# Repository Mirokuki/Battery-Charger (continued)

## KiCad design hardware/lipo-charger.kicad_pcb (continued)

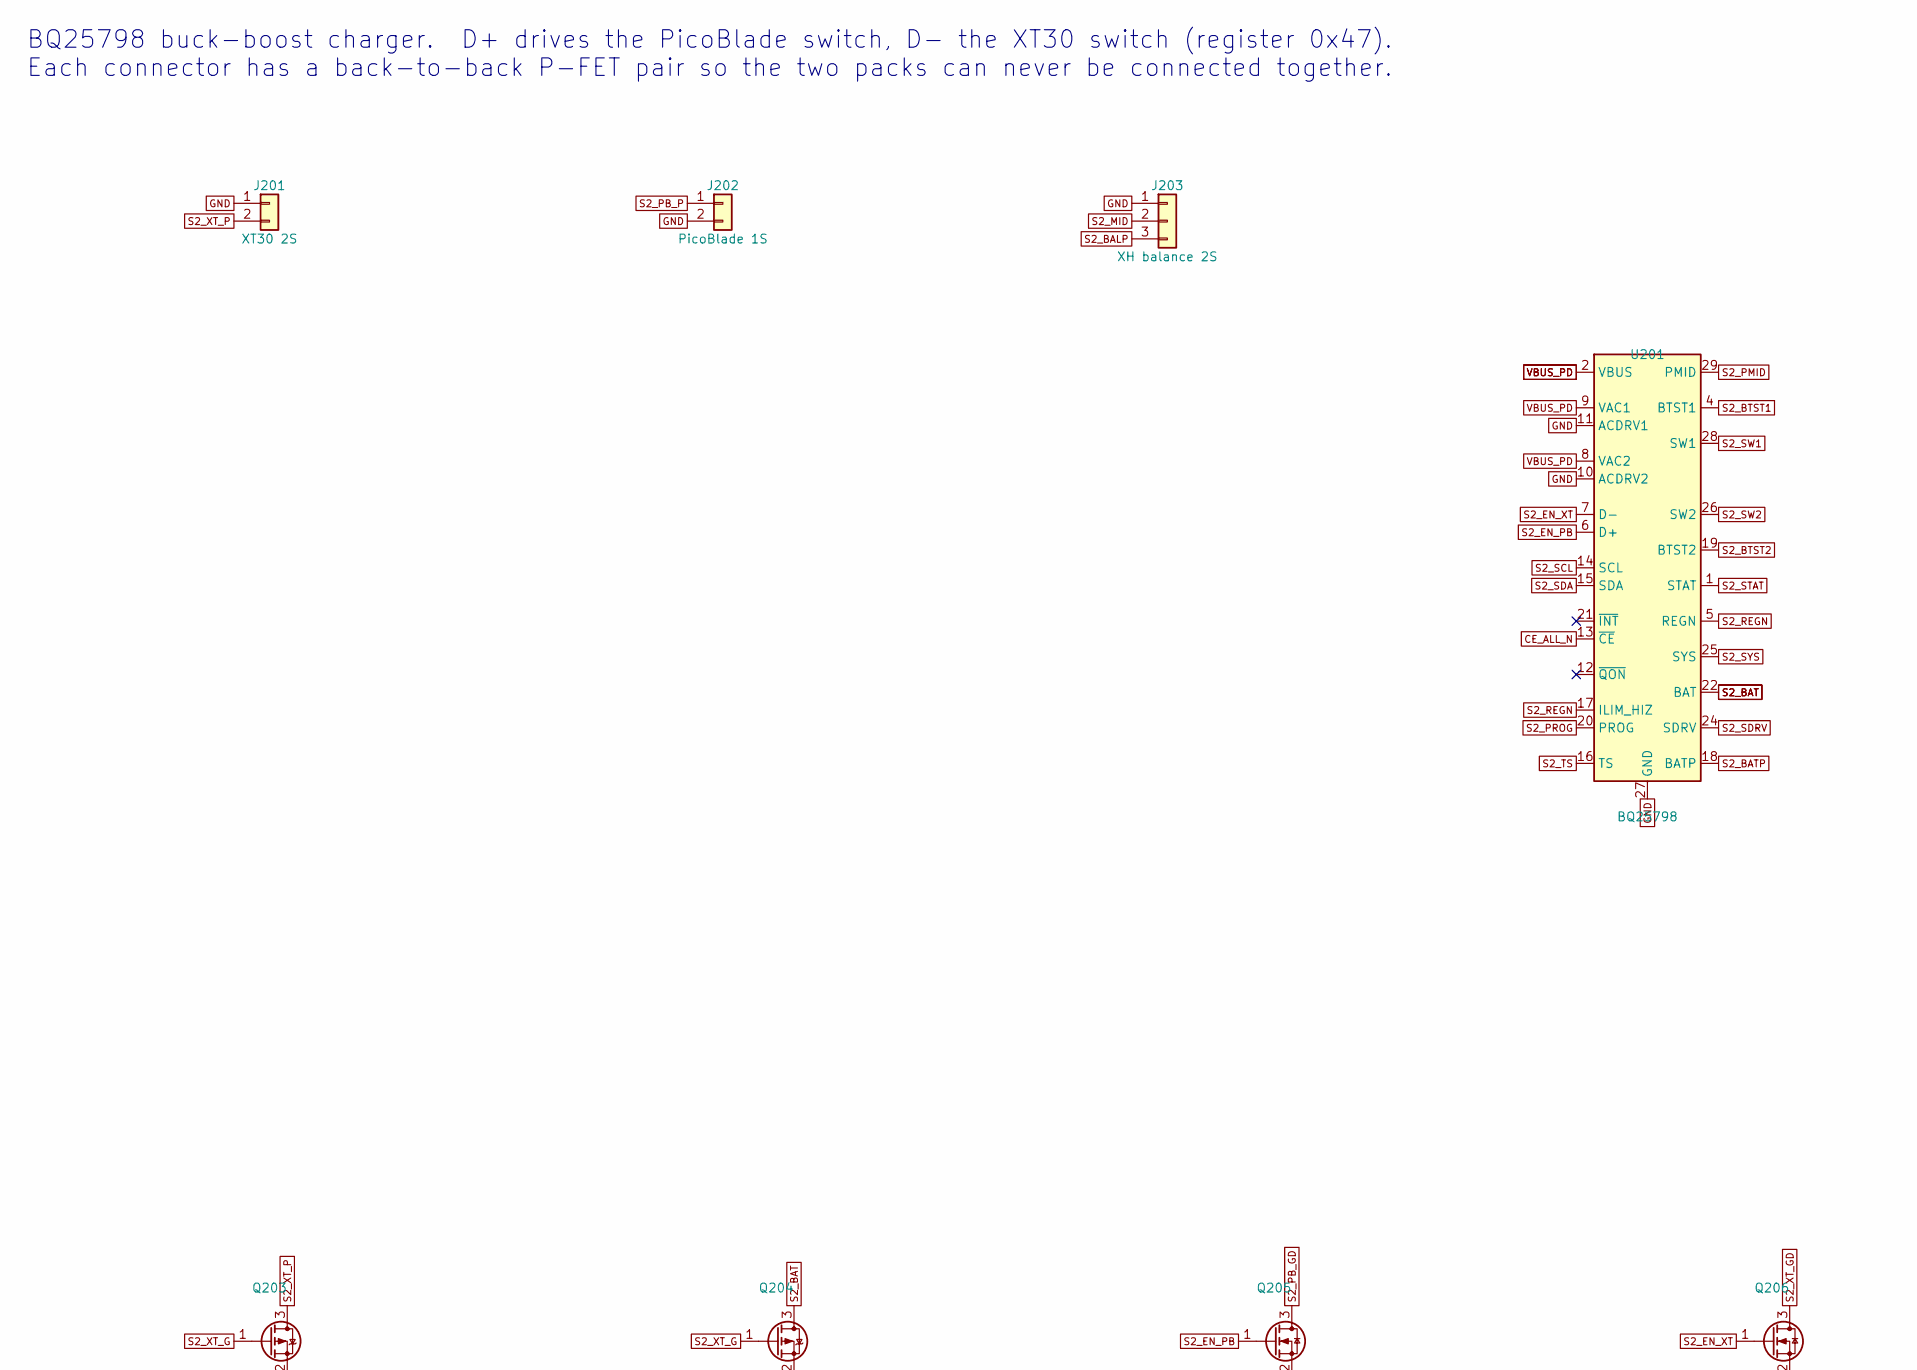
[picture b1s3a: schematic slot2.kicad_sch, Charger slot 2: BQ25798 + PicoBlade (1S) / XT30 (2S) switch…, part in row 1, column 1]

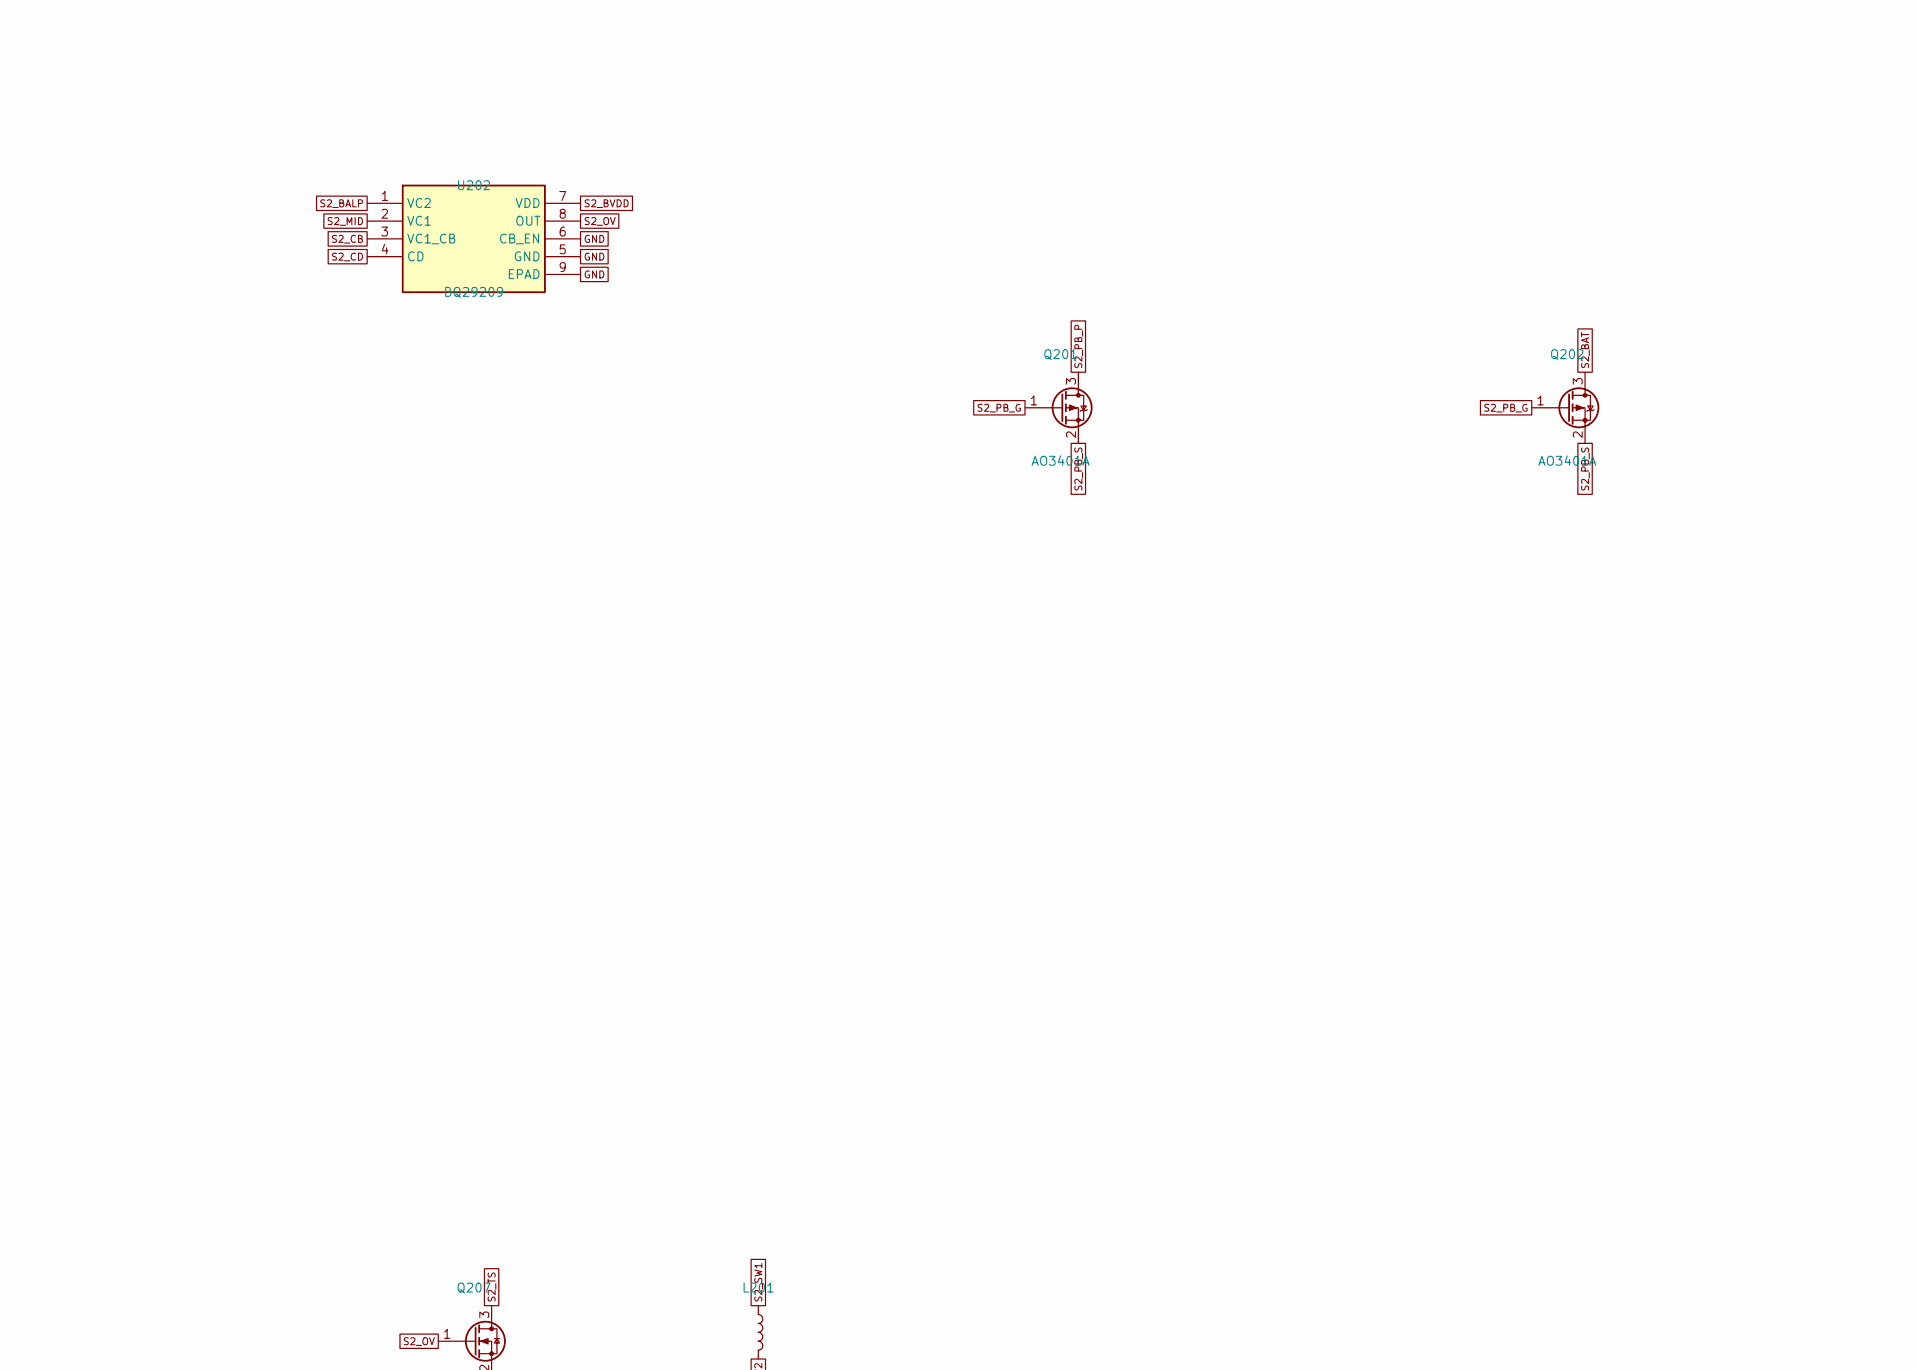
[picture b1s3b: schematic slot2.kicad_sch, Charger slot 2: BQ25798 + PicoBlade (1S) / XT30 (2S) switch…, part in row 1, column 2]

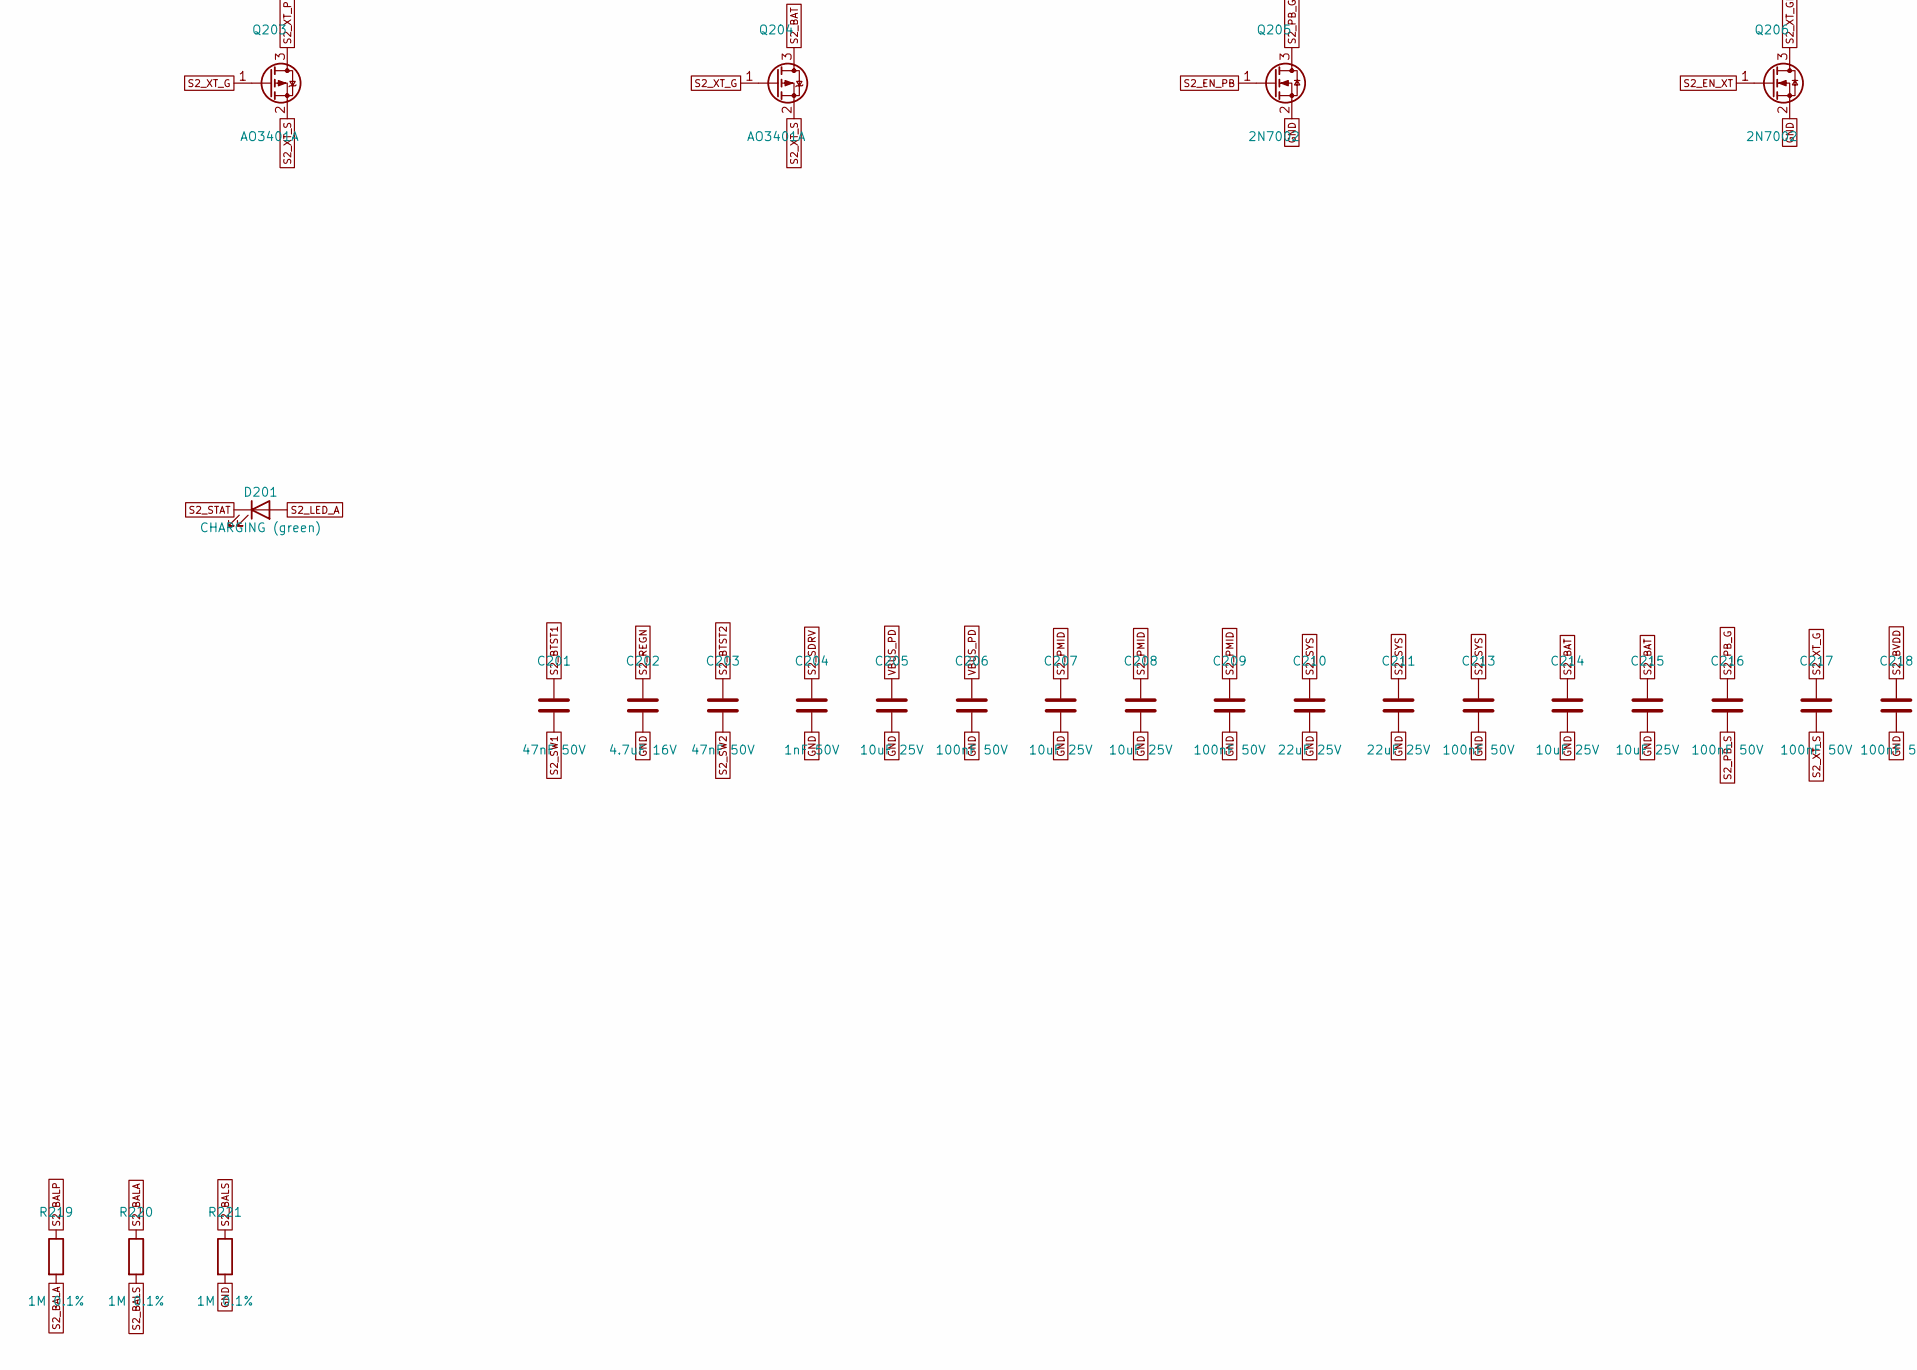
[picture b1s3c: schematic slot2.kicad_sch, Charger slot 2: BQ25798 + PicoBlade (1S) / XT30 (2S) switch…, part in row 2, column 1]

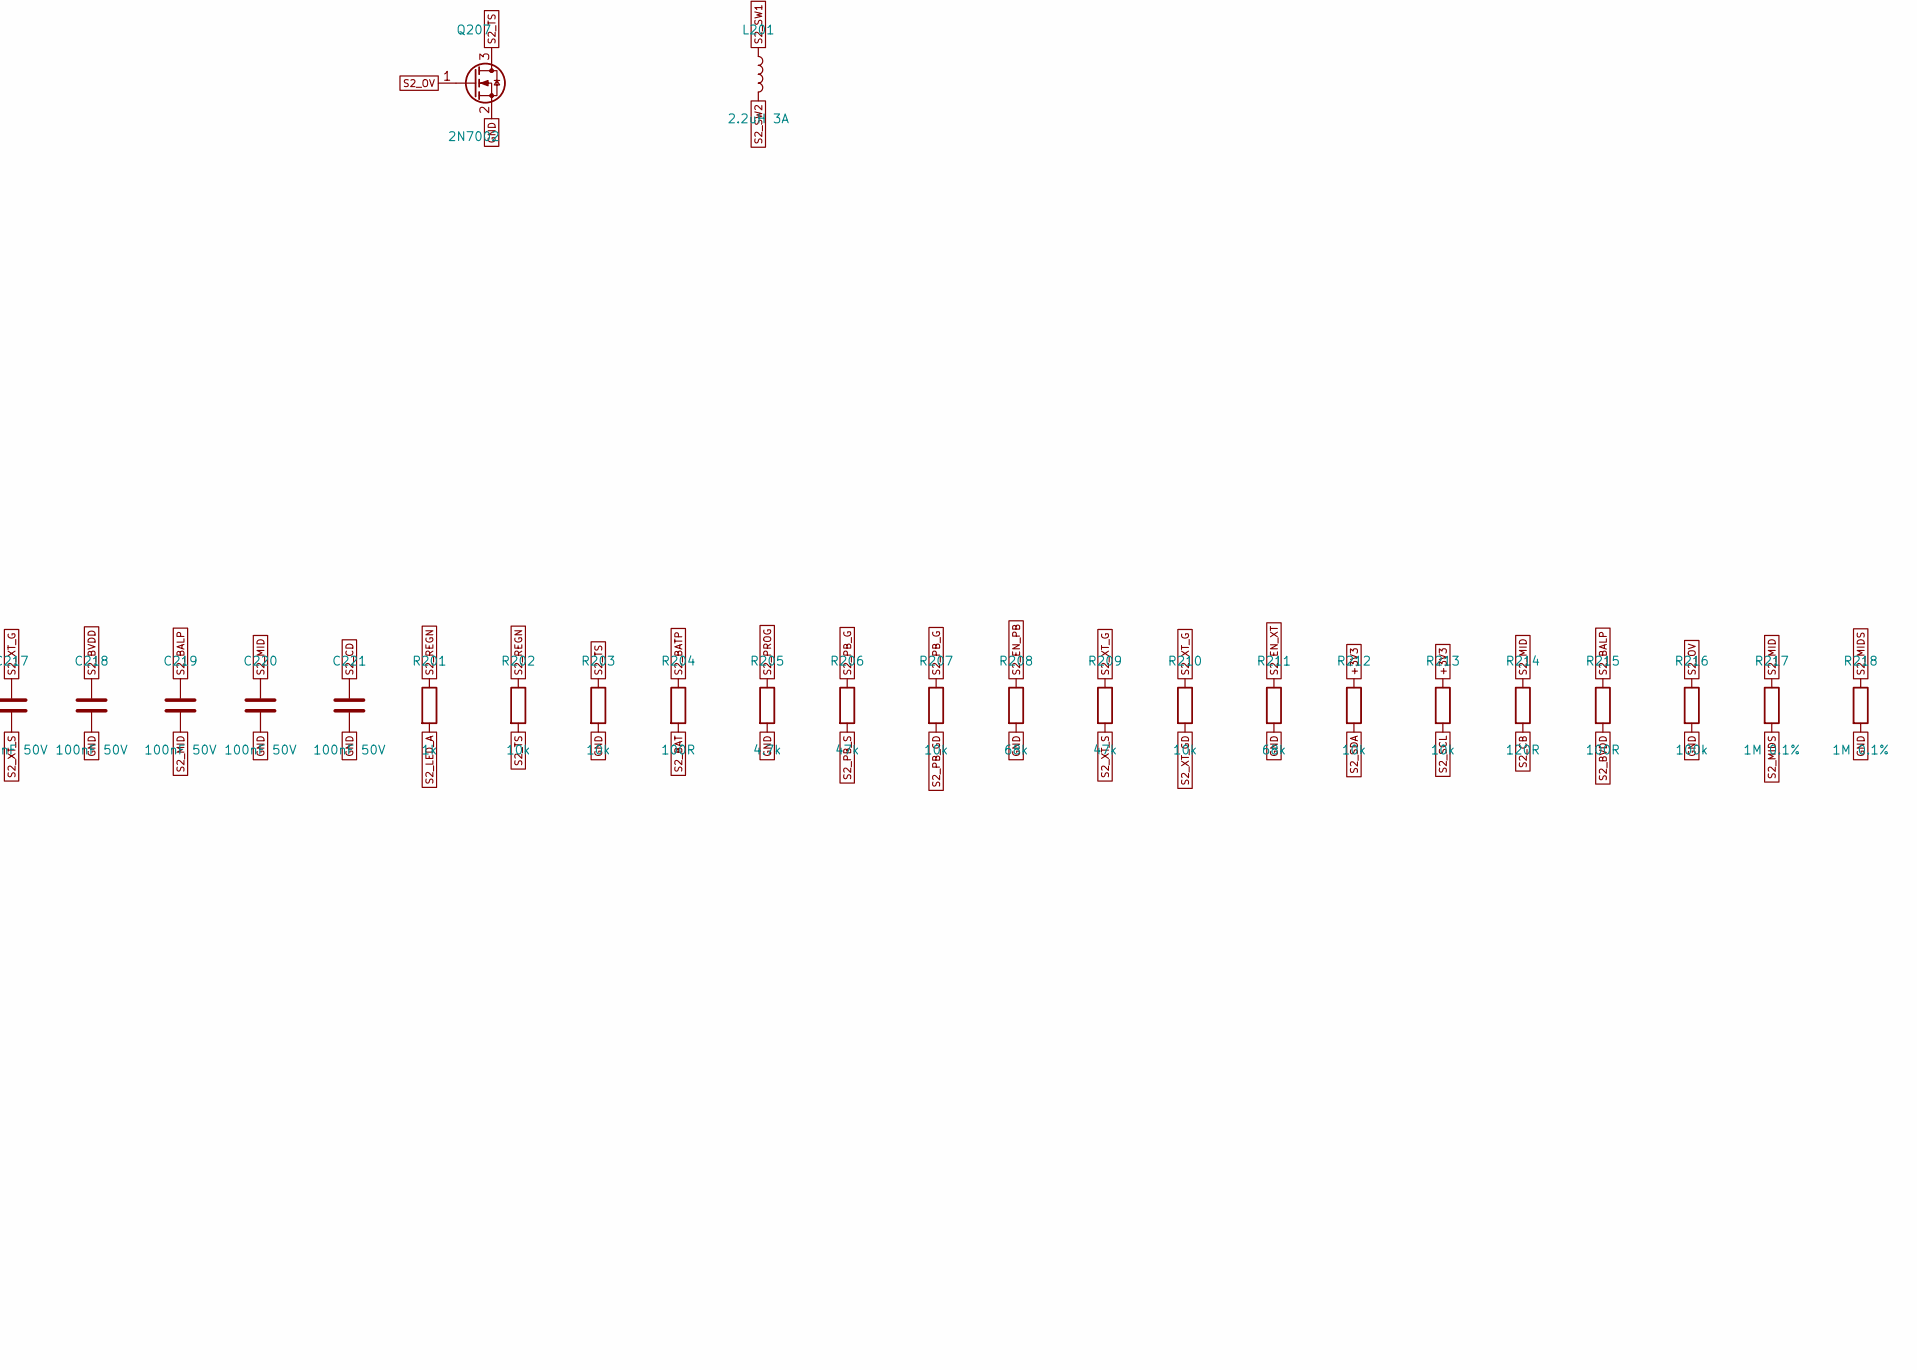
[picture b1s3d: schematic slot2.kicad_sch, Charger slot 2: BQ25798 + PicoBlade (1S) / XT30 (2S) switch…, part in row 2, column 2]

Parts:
C201, C203: 47nF 50V; C_0402_1005Metric; MPN CL05B473KB5NNNC
C202: 4.7uF 16V; C_0603_1608Metric; MPN CL10A475KO8NNNC; LCSC C19666
C204: 1nF 50V; C_0402_1005Metric; MPN CL05B102KB5NNNC; LCSC C1523
C205, C207, C208, C214, C215: 10uF 25V; C_0805_2012Metric; MPN CL21A106KAYNNNE; LCSC C15850
C206, C209, C213, C216, C217, C218, C219, C220, C221: 100nF 50V; C_0402_1005Metric; MPN CL05B104KB54PNC; LCSC C307331
C210, C211: 22uF 25V; C_0805_2012Metric; MPN CL21A226MAQNNNE; LCSC C45783
D201: CHARGING (green); LED_0603_1608Metric; MPN 19-217/GHC-YR1S2/3T; LCSC C72043
J201: XT30 2S; AMASS_XT30UPB-M_1x02_P5.0mm_Vertical; MPN XT30UPB-M; LCSC C99101
J202: PicoBlade 1S; Molex_PicoBlade_53047-0210_1x02_P1.25mm_Vertical; MPN 0530470210
J203: XH balance 2S; JST_XH_B3B-XH-A_1x03_P2.50mm_Vertical; MPN B3B-XH-A; LCSC C144394
L201: 2.2uH 3A; L_Changjiang_FNR4030S; MPN FNR4030S2R2MT
Q201, Q202, Q203, Q204: AO3401A; SOT-23; MPN AO3401A; LCSC C15127
Q205, Q206, Q207: 2N7002; SOT-23; MPN 2N7002; LCSC C8545
R201: 1k; R_0402_1005Metric; MPN 0402WGF1001TCE; LCSC C11702
R202, R203, R207, R210, R212, R213: 10k; R_0402_1005Metric; MPN 0402WGF1002TCE; LCSC C25744
R204, R215: 100R; R_0402_1005Metric; MPN 0402WGF1000TCE; LCSC C25076
R205: 4.7k; R_0402_1005Metric; MPN 0402WGF4701TCE; LCSC C25900
R206, R209: 47k; R_0402_1005Metric; MPN 0402WGF4702TCE; LCSC C25792
R208, R211: 68k; R_0402_1005Metric; MPN 0402WGF6802TCE; LCSC C36871
R214: 120R; R_0402_1005Metric; MPN 0402WGF1200TCE
R216: 100k; R_0402_1005Metric; MPN 0402WGF1003TCE; LCSC C25741
R217, R218, R219, R220, R221: 1M 0.1%; R_0402_1005Metric; MPN RT0402BRD071ML
U201: BQ25798; Texas_RQM0029A_VQFN-29_4x4mm_P0.4mm; MPN BQ25798RQMR; LCSC C2876768
U202: BQ29209; VSON-8-1EP_3x3mm_P0.65mm_EP1.65x2.4mm; MPN BQ29209DRBR

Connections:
+3V3: R212.1, R213.1; also elsewhere on the board
CE_ALL_N: U201.13 (~CE); also elsewhere on the board
GND: C202.2, C204.2, C205.2, C206.2, C207.2, C208.2, C209.2, C210.2, C211.2, C213.2, C214.2, C215.2, C218.2, C220.2, C221.2, J201.1, J202.2, J203.1, Q205.2 (S), Q206.2 (S), Q207.2 (S), R203.2, R205.2, R208.2, R211.2, R216.2, R218.2, R221.2, U201.10 (ACDRV2), U201.11 (ACDRV1), U201.27 (GND), U202.5 (GND), U202.6 (CB_EN), U202.9 (EPAD); also elsewhere on the board
S2_BALA: R219.2, R220.1
S2_BALP: C219.1, J203.3, R215.1, R219.1, U202.1 (VC2)
S2_BALS: R220.2, R221.1; also elsewhere on the board
S2_BAT: C214.1, C215.1, Q202.3 (D), Q204.3 (D), R204.2, U201.22 (BAT), U201.23 (BAT)
S2_BATP: R204.1, U201.18 (BATP)
S2_BTST1: C201.1, U201.4 (BTST1)
S2_BTST2: C203.1, U201.19 (BTST2)
S2_BVDD: C218.1, R215.2, U202.7 (VDD)
S2_CB: R214.2, U202.3 (VC1_CB)
S2_CD: C221.1, U202.4 (CD)
S2_EN_PB: Q205.1 (G), R208.1, U201.6 (D+)
S2_EN_XT: Q206.1 (G), R211.1, U201.7 (D-)
S2_LED_A: D201.2 (A), R201.2
S2_MID: C219.2, C220.1, J203.2, R214.1, R217.1, U202.2 (VC1)
S2_MIDS: R217.2, R218.1; also elsewhere on the board
S2_OV: Q207.1 (G), R216.1, U202.8 (OUT)
S2_PB_G: C216.1, Q201.1 (G), Q202.1 (G), R206.1, R207.1
S2_PB_GD: Q205.3 (D), R207.2
S2_PB_P: J202.1, Q201.3 (D)
S2_PB_S: C216.2, Q201.2 (S), Q202.2 (S), R206.2
S2_PMID: C207.1, C208.1, C209.1, U201.29 (PMID)
S2_PROG: R205.1, U201.20 (PROG)
S2_REGN: C202.1, R201.1, R202.1, U201.5 (REGN), U201.17 (ILIM_HIZ)
S2_SCL: R213.2, U201.14 (SCL); also elsewhere on the board
S2_SDA: R212.2, U201.15 (SDA); also elsewhere on the board
S2_SDRV: C204.1, U201.24 (SDRV)
S2_STAT: D201.1 (K), U201.1 (STAT)
S2_SW1: C201.2, L201.1, U201.28 (SW1)
S2_SW2: C203.2, L201.2, U201.26 (SW2)
S2_SYS: C210.1, C211.1, C213.1, U201.25 (SYS)
S2_TS: Q207.3 (D), R202.2, R203.1, U201.16 (TS)
S2_XT_G: C217.1, Q203.1 (G), Q204.1 (G), R209.1, R210.1
S2_XT_GD: Q206.3 (D), R210.2
S2_XT_P: J201.2, Q203.3 (D)
S2_XT_S: C217.2, Q203.2 (S), Q204.2 (S), R209.2
VBUS_PD: C205.1, C206.1, U201.2 (VBUS), U201.3 (VBUS), U201.8 (VAC2), U201.9 (VAC1); also elsewhere on the board

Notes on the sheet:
BQ25798 buck-boost charger. D+ drives the PicoBlade switch, D- the XT30 switch (register 0x47). Each connector has a back-to-back P-FET pair so the two packs can never be connected together.
